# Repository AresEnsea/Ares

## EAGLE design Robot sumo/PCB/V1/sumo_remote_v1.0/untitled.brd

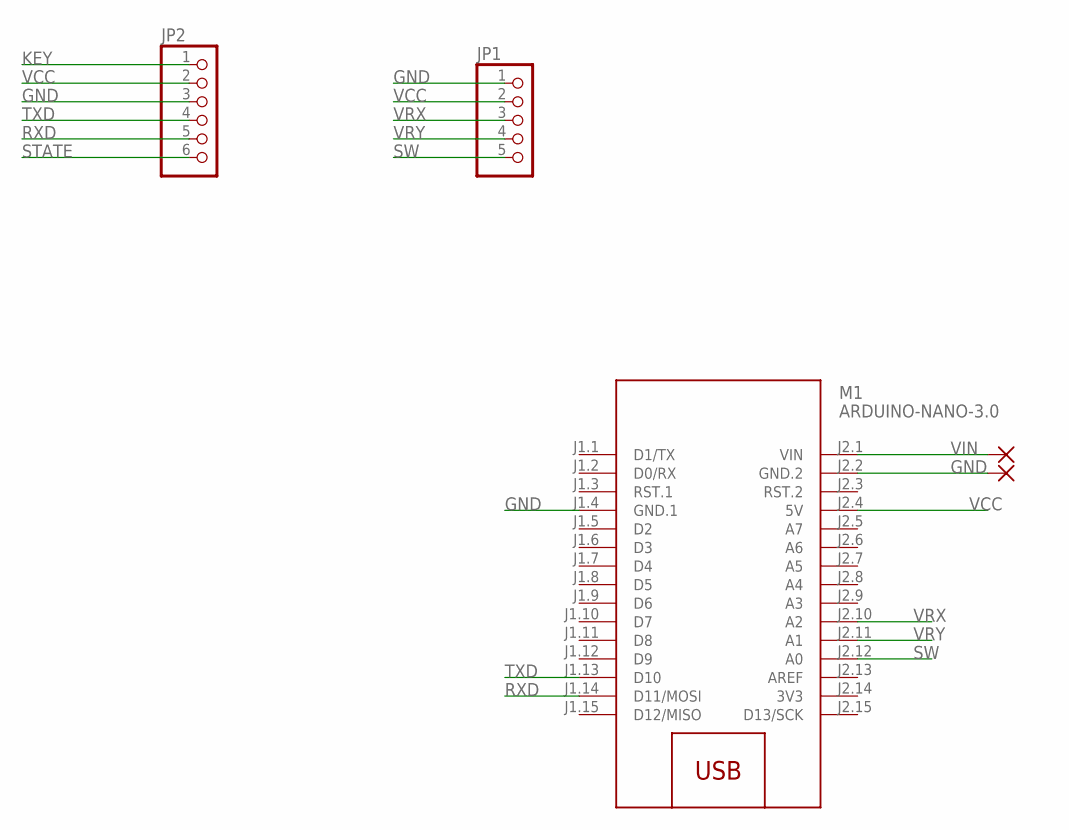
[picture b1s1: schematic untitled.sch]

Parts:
JP1: PINHD-1X5; 1X05
JP2: PINHD-1X6; 1X06
M1: ARDUINO-NANO-3.0
PAD1, PAD2: WIREPADSMD5-2,5; 5-2,5

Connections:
3V3: M1.J2.14 (3V3)
GND: JP1.1, JP2.3, M1.J1.4 (GND.1), M1.J2.2 (GND.2), PAD2.1
KEY: JP2.1
RXD: JP2.5, M1.J1.14 (D11/MOSI)
STATE: JP2.6
SW: JP1.5, M1.J2.12 (A0)
TXD: JP2.4, M1.J1.13 (D10)
VCC: JP1.2, JP2.2, M1.J2.4 (5V)
VIN: M1.J2.1 (VIN), PAD1.1
VRX: JP1.3, M1.J2.10 (A2)
VRY: JP1.4, M1.J2.11 (A1)

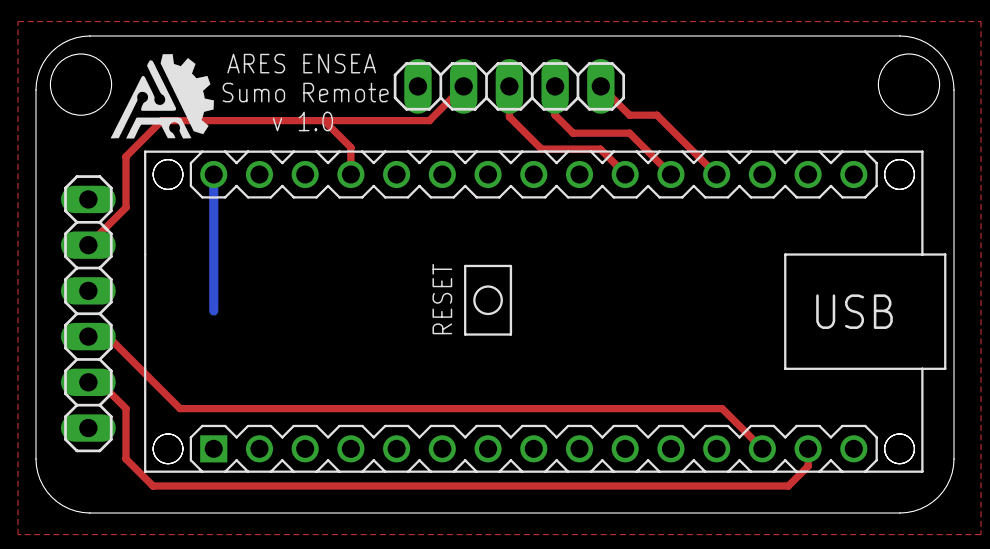
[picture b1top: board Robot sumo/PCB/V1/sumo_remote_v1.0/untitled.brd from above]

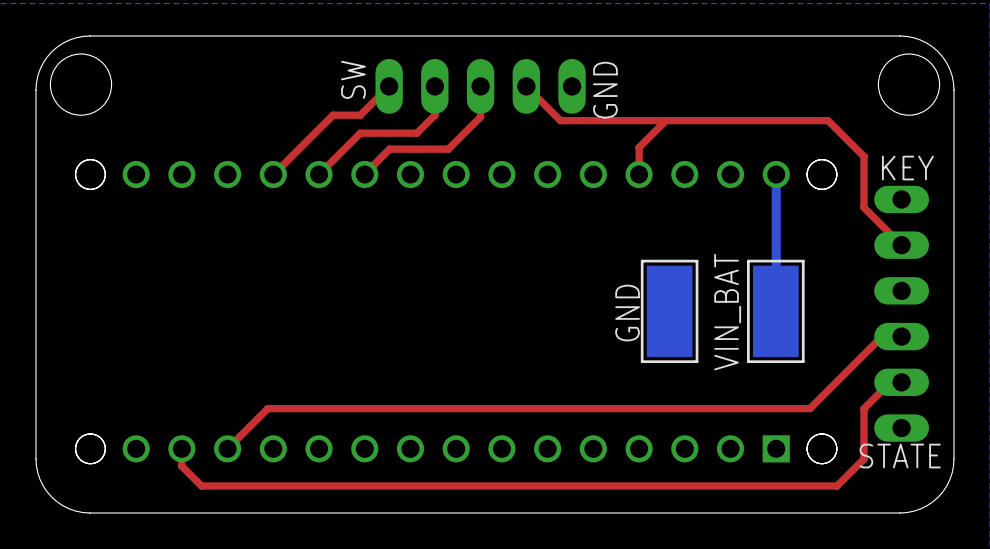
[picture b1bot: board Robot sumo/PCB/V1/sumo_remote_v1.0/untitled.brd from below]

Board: 2 copper layers, 51.0 x 26.5 mm, 5 parts (2 on the bottom side), 8 nets.

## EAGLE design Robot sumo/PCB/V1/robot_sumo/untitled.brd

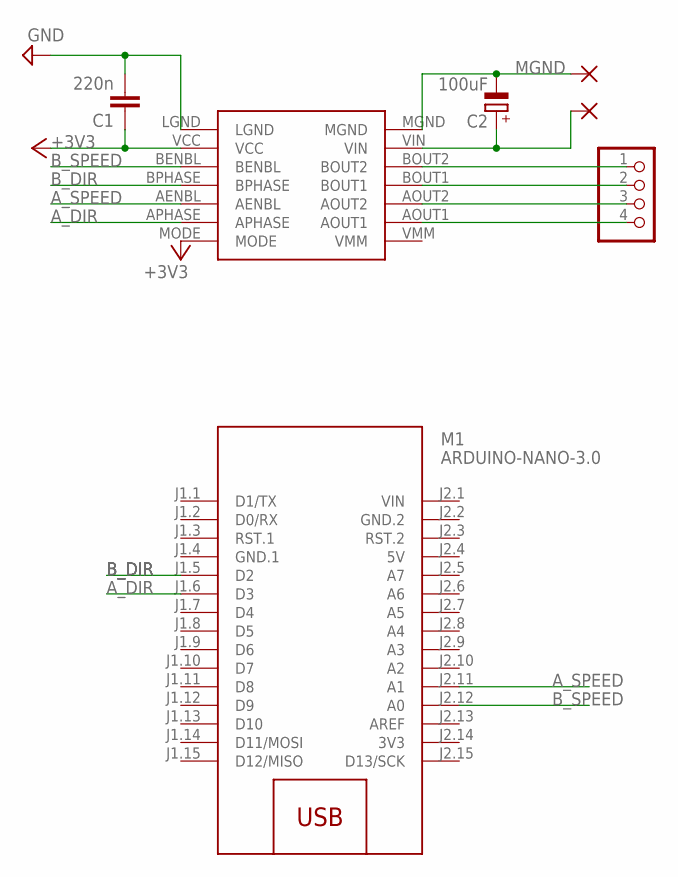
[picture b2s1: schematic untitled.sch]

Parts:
C1: 220n; C025-025X050
C2: 100uF; E3,5-8
GND: WIREPADSMD5-1,8; 5-1,8
JP1: PINHD-1X4; 1X04
M1: ARDUINO-NANO-3.0
U$1: POLOLU_MOTOR_DRV8835THROUGHHOLE; POLOLU_MOTOR_DRV_DRV8835
VIN_BAT: WIREPADSMD5-1,8; 5-1,8

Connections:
3V3: M1.J2.14 (3V3)
5V: M1.J2.4 (5V)
+3V3: C1.1, U$1.MODE, U$1.VCC
A_DIR: M1.J1.6 (D3), U$1.APHASE
A_SPEED: M1.J2.11 (A1), U$1.AENBL
B_DIR: M1.J1.5 (D2), U$1.BPHASE
B_SPEED: M1.J2.12 (A0), U$1.BENBL
GND: C1.2, U$1.LGND
GND.1: M1.J1.4 (GND.1)
GND.2: M1.J2.2 (GND.2)
MGND: C2.-, GND.1, U$1.MGND
unnamed: C2.+, U$1.VIN, VIN_BAT.1
unnamed: JP1.1, U$1.BOUT2
unnamed: JP1.2, U$1.BOUT1
unnamed: JP1.3, U$1.AOUT2
unnamed: JP1.4, U$1.AOUT1
VIN: M1.J2.1 (VIN)

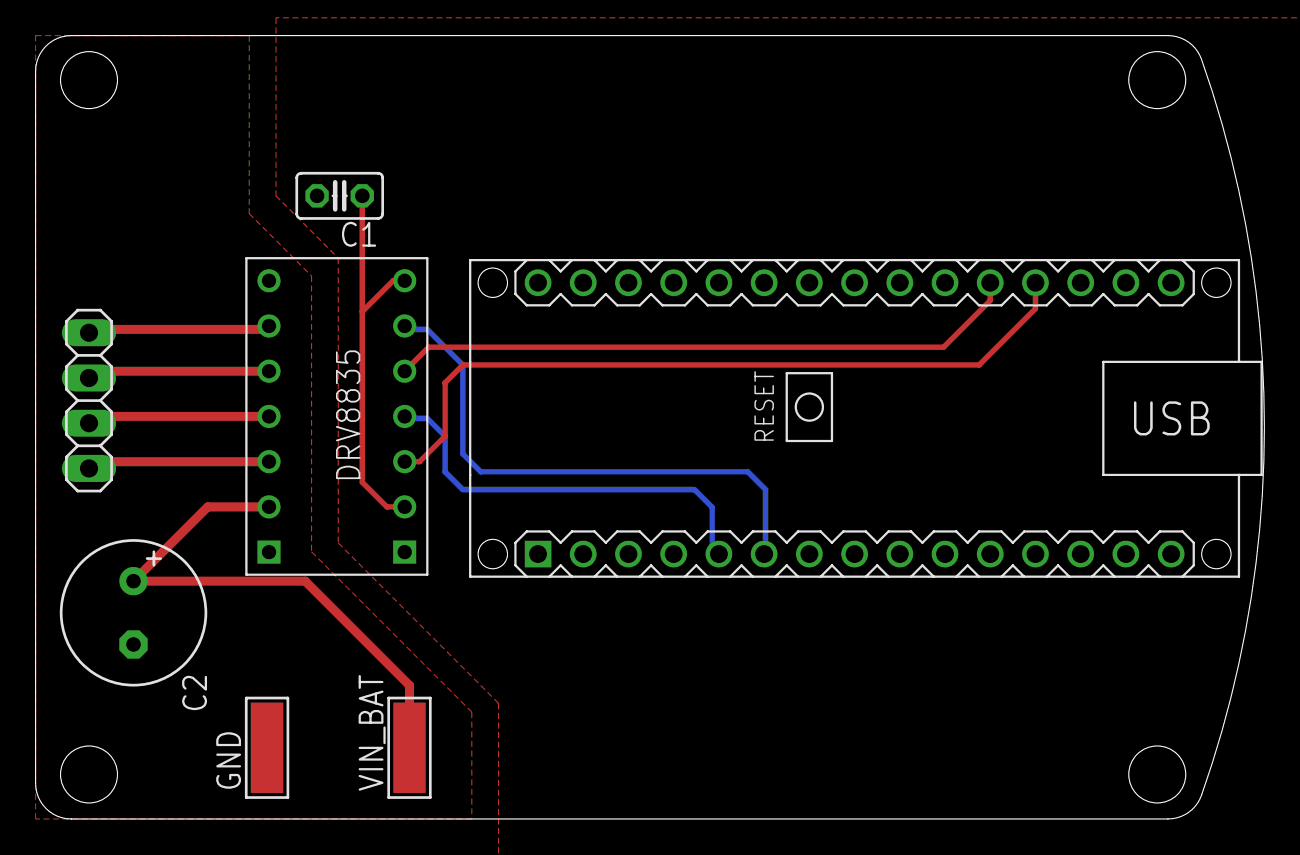
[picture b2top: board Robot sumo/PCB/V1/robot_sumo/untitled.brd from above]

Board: 2 copper layers, 69.0 x 44.0 mm, 7 parts (0 on the bottom side), 12 nets.

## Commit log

2022-10-07 majcodesumo
2022-10-20 AX12Add
2022-10-26 AXandF303
2022-10-29 V6sumo
2022-11-06 sumobotOk
2022-11-09 sumobotBackwardVer
2022-11-22 ecran
2022-11-24 faire fonctionner les ecrans sans touch
    voir https://github.com/afiskon/stm32-ili9341
2023-01-26 join
2023-01-26 newSumoRoobot
2023-02-02 V8Lipo
2023-08-28 Ajout du dossier Activité de rentrée 2023
2023-08-28 Corrections mineures
2023-11-18 Ajout des activités de rentrée
2023-11-18 Ajout du dossier Borne d'arcade
2023-11-23 added Sumo V2 project
2023-11-23 Added BOM
2024-01-18 ajout des models 3D du sumoBot

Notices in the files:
parts and their libraries:
diy-modules: Released under the Creative Commons Attribution 4.0 International License: http://creativecommons.org/licenses/by/4.0
